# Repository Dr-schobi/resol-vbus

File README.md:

# resol-vbus

#### A JavaScript library for processing RESOL VBus data.

## Library is in maintenance mode!

> ...
>
> As a result of this shift of focus the resol-vbus library has entered maintenance mode. It will still receive security update when necessary over the course of the next months, but no additional improvements will be implemented here.
>
> ...

See [this issue](https://github.com/danielwippermann/resol-vbus/issues/110) for details.

## Features

* Connects to various RESOL VBus devices
* Processes live and recorded VBus data streams
* Discovers LAN-enabled RESOL devices on the local network
* Allows to send parameterization commands to a controller
* Synchronizes recorded VBus data from a RESOL datalogger to your local file system
* Converts recorded VBus data into human or machine readable formats, optionally allowing to filter the output

## Documentation

You can find the work-in-progress documentation for this project here:

[http://danielwippermann.github.io/resol-vbus/](http://danielwippermann.github.io/resol-vbus/)

The JSDoc-generated documentation is located here:

[http://danielwippermann.github.io/resol-vbus/#/jsdoc](http://danielwippermann.github.io/resol-vbus/#/jsdoc)

## Installation

If you want to use this module in your own application, you can just install it from the npm registry:

	⌘  npm install --save resol-vbus

If you want to contribute to it you might want to check out the latest version from GitHub:

	⌘  git clone https://github.com/danielwippermann/resol-vbus.git
	⌘  cd resol-vbus
	⌘  npm install

## Running the console examples

	⌘  node examples/<name>/index.js

## Running the tests

To start a single run of the test suite just enter the following command
into your shell:

	⌘  npm test

To run the tests after each change to the source just enter the
following command into your shell:

	⌘  npm test -- --watch

## Supported Devices & Services

* [All current RESOL controllers with VBus](http://www.resol.de/index/produkte/sprache/en)
* [RESOL DL2 Datalogger](http://www.resol.de/index/produktdetail/kategorie/2/sprache/en/id/12)
* [RESOL DL3 Datalogger](http://www.resol.de/index/produktdetail/kategorie/2/sprache/en/id/86)
* [RESOL KM2 Communication module](http://www.resol.de/index/produktdetail/kategorie/2/id/209/sprache/en)
* [RESOL VBus/LAN interface adapter](http://www.resol.de/index/produktdetail/kategorie/2/id/76/sprache/en)
* [RESOL VBus/USB interface adapter](http://www.resol.de/index/produktdetail/kategorie/2/id/13/sprache/en)
* [RESOL VBus.net](http://www.vbus.net/)

## Technical Information & Specifications

* [RESOL VBus Google Group](https://groups.google.com/forum/#!forum/resol-vbus)
* [RESOL VBus Protocol Specification](http://danielwippermann.github.io/resol-vbus/#/md/docs/vbus-specification)
* [RESOL VBus Packet List](http://danielwippermann.github.io/resol-vbus/#/vsf)
* [RESOL VBus Recording File Format](http://danielwippermann.github.io/resol-vbus/#/md/docs/vbus-recording-file-format)
* [RESOL VBus Specification File Format v1](http://danielwippermann.github.io/resol-vbus/#/md/docs/vbus-specification-file-format-v1)
* [RESOL VBus over TCP Specification](http://danielwippermann.github.io/resol-vbus/#/md/docs/vbus-over-tcp)
* [RESOL DL2 (v2) & DL3 Data Download API](http://danielwippermann.github.io/resol-vbus/#/md/docs/dlx-data-download-api)

## Known issues

- The `ConfigurationOptimizers` do not yet detect the firmware version running on the controller to be configured.
  That sometimes causes configuration loads and saves to fail because unknown values are read from or written to
  (e.g. using the "customizer" example on a DeltaSol MX with firmware version 1.11 or below).

## Projects using `resol-vbus`

- https://github.com/BenniG82/vbus-to-homie

## Changelog

## Version 0.29.0 (2024-01-22)

- [BREAKING CHANGE] Changed IPv6 device discovery support activation.
    Previously the `options` object passed into `TcpDataSourceProvider#discoverDevices`
    needed an `ipv6` boolean value set to `true`. That option was removed in favor of a
    `family` string value which defaults to `"IPv4"` but can be set to `"IPv6"` to
    perform a IPv6 device discovery. In that case the two other options `localAddress`
    and `broadcastInterface` are required as well. See the documentation for more details.
- Add verifiers for VBus-over-TCP commands to `TcpConnectionEndpoint`.
- Add `connectionAttemptFailed` event to `TcpConnectionEndpoint`.

## Version 0.28.0 (2024-01-06)

- Add `extendFieldData` option to `DLxJsonConverter`.
- Add `SpecificationFile#getPacketTemplate`.
- Add password and channel checks to TCP endpoint. (#93)
- Add `TcpConnection#disableReconnect`.
- Correctly propagate errors during `TcpConnection` reconnect.

## Version 0.27.0 (2022-03-09)

- Fix bugs in `SerialConnection` and `SerialDataSourceProvider`

## Version 0.26.0 (2022-12-18, never released publicly)

- [BREAKING CHANGE] Removed `Recorder`, `DLxRecorder` and `FileSystemRecorder`
    The `Recorder` style of interfaces was not well thought out and unreliable. This
    version removes it, with no replacement!
- [BREAKING CHANGE] Removed `lodash` dependency
    Although this removal was done with great caution and a lot of test coverage, there
    might be side effects we have not thought of.

## Version 0.25.0 (2022-04-12)

- Update several dependencies to fix security issues.
- Update VBus specification file to 20220206.
- Add support for CRC7 in protocols using minor version 1.
- Add `Datagram` and `Telegram` support to `VBusRecordingConverter`.

## Version 0.24.0 (2021-09-12)

- [BREAKING CHANGE] Replaced the deprecated "request" dependency with Fetch API impl
    Since the "request" dependency that was used in the `DLxRecorder` class has
    been deprecated, the code was refactored to use a Fetch API implementation instead.
    But since the method `DLxRecorder#downloadToStream` expected "request"-specific options,
    it had to be changed, too. This method was renamed to `DLxRecorder#_downloadToStream` to
    indicate that it is a class-private method and its signature was changed to accept
    Fetch API specific options.

## Version 0.23.0 (2021-05-14)

- [BREAKING CHANGE] Replacing custom inheritance code with `class` syntax
    Up to this version inheritance was established using a custom `extend` function.
    Since only modern ECMAscript runtimes are supported since the last release the code was
    refactored to use the ECMAscript `class` syntax instead. In that process the `extend`
    function was removed, both the standalone one and the static class function that was
    added to every "class".
- [BREAKING CHANGE] Returning a `Promise` from `channelListCallback` callback
    The `TcpConnection` accepts a `channelListCallback`. This callback gets called with the
    list of channels returned from the `CHANNELLIST` command and a `done` callback.

    Up to this version the return value of the `channelListCallback` was ignored. Starting
    with this version this behaviour is changed if the return value of the callback is
    a `Promise`:
    - if the `Promise` reject, the `done` callback is automatically called with `done(reason)`
    - if the `Promise` resolves, the `done` callback is automatically called with
      `done(null, result)`

    This allows the `channelListCallback` to be `async`.
- Errors thrown by `TcpConnection#connect` now have a `vbusPhase` member describing on which
  VBus-over-TCP command the error occurred

## Version 0.22.0 (2021-05-10)

- [BREAKING CHANGE] Dropping support for Node.js versions < 12

## Version 0.21.0 (2020-05-02)

- [BREAKING CHANGE] Returning a `Promise` from `filterPacket` or `filterDatagram` callbacks
    The `Connection#transceive` method and many of the helper methods that use it
    accept a `filterPacket` and/or `filterDatagram` callback. Those callbacks get called
    with the data to filter and a `done` callback.

    Up to this version the return value of the filter callbacks was ignored. Starting with
    this version this behaviour is changed if the return value of the filter callbacks is
    a `Promise`:
    - if the `Promise` rejects, the `done` callback is automatically called with `done(reason)`
    - if the `Promise` resolves with `null` or `undefined`, the `done` callback is not called
    - if the `Promise` resolves with any other result, the `done` callback is automatically
      called with `done(null, result)`

    This allows `async` filter callbacks!
- Add `SerialConnection#baudrate` option.
- Stop running Travis tests under Node 6.
    Some dependency of `jest` does not work under Node 6 making tests break
    for that target. The `resol-vbus` library itself might still work under
    Node 6, but there is no guarantee...

## Version 0.20.0 (2019-06-15)

- This version contains several breaking changes! You have been warned...
	- Refactor code to make use of ES2018 features (using Babel to back-support up to Node.js 6)
	- Remove custom `Promise` implementation in favor of built-in, native one.
	- `Promise` return values no longer provide the `finally` and `done` methods.
	- Remove `utils.promise`, `utils.Promise` and `utils.cancelablePromise`.
	- Add `reportProgress` and `checkCanceled` options to `ConnectionCustomizer#transceive{Configuration,Value}` as a replacement to the previously used `cancelablePromise` solution.
- Add RESOL DeltaSol C configuration optimizer.
- Add support for VBus-over-TCP wrapped in TLS.

## Version 0.17.0 (2018-02-10)

- Add `Buffer` support to `Connection#(get|set)ValueById` for values larger than 32-bit.
- Add `Connection#getCaps1`.
- Add bulk value transaction support to `Connection` class.
- Add support to generate and parse "type 9" comment records using `VBusRecordingConverter`.
- Make it easier to create a `Specification` from a `SpecificationFile`.
- Extend `vbustouch-proxy` example with text data logging feature.
- Update dependencies.
- Some minor bug fixes.

### Version 0.16.0 (2017-02-01)

- Use VSF binary file to load VBus specification data
- Add support to read and write raw data in VBus recordings
- Extend `VBusRecordingConverter` to support fast topology-only scan
- Code clean up
- Several minor bug fixes

### Version 0.15.0 (2016-03-30)

- Update VBus specification data
- Several minor bug fixes

### Version 0.14.0 (2015-10-29)

- Improve configuration optimizers and their discovery
- Update VBus specification data

### Version 0.13.0 (2015-05-14)

- Add configuration optimizers for RESOL DeltaSol SLT
- Add BlockType support

### Version 0.12.2 (2015-05-05)

- Update VBus specification data

### Version 0.12.1 (2015-04-27)

- Add configuration optimizers for RESOL DeltaSol MX and BS/4 v2
- Add a simple JSON live data server example
- Add some documentation
- Several bug fixes

### Version 0.12.0 (2015-02-28)

- Add `vbustouch-proxy` example
- Add support for rounding floating point numbers

### Version 0.11.1 (2014-11-04)

- Fix a floating point bug caused by `setRawValue`

### Version 0.11.0 (2014-10-29)

- Added support for setting packet field values
- Several bug fixes

### Version 0.10.0 (2014-04-26)

- Finalized support for customizing controller configuration.
- Several bug fixes.

### Version 0.9.0 (2014-03-16)

- Completed Recorder class by adding support for recording
- Added unit conversion to VBus specification
- Several bug fixes.

### Version 0.8.0 (2014-03-03)

- Extended Converter and VBusRecordingConverter to support object mode in stream (for performance reason)
- Fixed several bugs
- Increased test coverage and completed documentation.

### Version 0.7.0 (2014-02-17)

First release to the NPM registry.

## Contributors

* Thorsten Müller
* Paul Hanna
* Sabine Käß
* Andrew Thompson (@thompsa)
* @t9zx
* @SurfGargano
* @epenet

## Legal Notices

RESOL, VBus, VBus.net and others are trademarks or registered trademarks
of RESOL - Elektronische Regelungen GmbH.

All other trademarks are the property of their respective owners.

## License

The MIT License (MIT)

Copyright (c) 2013-present, Daniel Wippermann.

Permission is hereby granted, free of charge, to any person obtaining a copy
of this software and associated documentation files (the "Software"), to deal
in the Software without restriction, including without limitation the rights
to use, copy, modify, merge, publish, distribute, sublicense, and/or sell
copies of the Software, and to permit persons to whom the Software is
furnished to do so, subject to the following conditions:

The above copyright notice and this permission notice shall be included in
all copies or substantial portions of the Software.

THE SOFTWARE IS PROVIDED "AS IS", WITHOUT WARRANTY OF ANY KIND, EXPRESS OR
IMPLIED, INCLUDING BUT NOT LIMITED TO THE WARRANTIES OF MERCHANTABILITY,
FITNESS FOR A PARTICULAR PURPOSE AND NONINFRINGEMENT. IN NO EVENT SHALL THE
AUTHORS OR COPYRIGHT HOLDERS BE LIABLE FOR ANY CLAIM, DAMAGES OR OTHER
LIABILITY, WHETHER IN AN ACTION OF CONTRACT, TORT OR OTHERWISE, ARISING FROM,
OUT OF OR IN CONNECTION WITH THE SOFTWARE OR THE USE OR OTHER DEALINGS IN
THE SOFTWARE.

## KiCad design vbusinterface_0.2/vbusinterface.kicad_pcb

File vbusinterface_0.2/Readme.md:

## Version 0.2 (2023-08)

While cleaning up, I came across the box of materials for this project and decided to finish this project.
The wires of the flying installation verion 0.0 have broken off in the meantime and the system was not operational.

Changes:
- re-draw with a new Kicad version (I wouldn't say I have lost them, but I stopped searching for the old files)
- integrate connectors, use [Wago 2604-1102](https://www.wago.com/global/pcb-terminal-blocks-and-pluggable-connectors/pcb-terminal-block/p/2604-1102)
- try to have it mostly assembled from JLCPCB to avoid stocking 10s of some exotic SMD components
- use an off-the shelf PoE splitter for providing the 5V without extra power supplies, option of barrel jack or micro-USB power connector
- integrate a mounting system, I decided to use the Phoenix Contact UMK system to have a DIN rail mount for everything. This requires [UMK-BE22.5](https://www.phoenixcontact.com/en-pc/products/base-element-umk-be-225-2970028), [UMK-SE11,25-3](https://www.phoenixcontact.com/en-pc/products/side-element-umk-se-1125-3-5030266), [UMK-11,25-1](https://www.phoenixcontact.com/en-pc/products/side-element-umk-se-1125-1-2970442) and [UMK-FE](https://www.phoenixcontact.com/en-pc/products/foot-element-umk-fe-2970031). This is a really cool configurable system which results in a really neat and sturdy mounting. (RANT:) However, the Phoenix Contact Website is completely useless for selecting which components one might want to use. There is no "compatible with" indication, no online configurator, not even a small quantity ordering process. I'm sure when I call them in a commercial setting from my day-job, a representative will show up immediately and explain the system to me. But as a hobbyist, this is unreachable. Individual parts online are more expensive than the assembled PCB. Sorry Phoenix Contact, but you've scared me away for any future use, even in my day-job.

really nice partially assembled PCBs as they arrived from JLCPCB

not so nice any more - with the needed fixes integrated

This is how the final system should look like. With options for USB-C and barrel-Jack power:

Conclusion:
- much nicer, but I introduced some errors
- when changing a few parts, even more can likely be assembled from "basic parts" directly, sparing me a load of new bags with individual SMD components

Errata:
- when designing a new component with Kicad, the default hole diameter is too small to fit a standard pin header. I had to use individual pieces of 0.4mm wire to mount my components U4 and U5
- the output to the TCP232 should be 3.3V only, but I was powering the 4093 stage with 5V. R3 needs to match. 
- for C1, I picked the wrong part from JLCPCB, should be 1nF instead of 1uF

(RANT on JLCPCB:) the JLCPCB parts selection is broken for me. For example, when searching for a "0805" resistor with a specific value, the parametric search does not gives too many results. When limiting to "basic parts" only, tjhe list is empty. Listing all "basic parts" "0805" resistors is possible, but they can't be sorted, the actual values in the list are cut off (I need to click though every part?). The Kicad Export with the Fabrication Toolkit is a really nice new way for single click export. But somehow the ICs are rotated the wrong way and the board dimensions for backside assembly are mixed up... In the end, this is still the best manufacturer for me, but I hesitate to pay more for shipping than for the product.

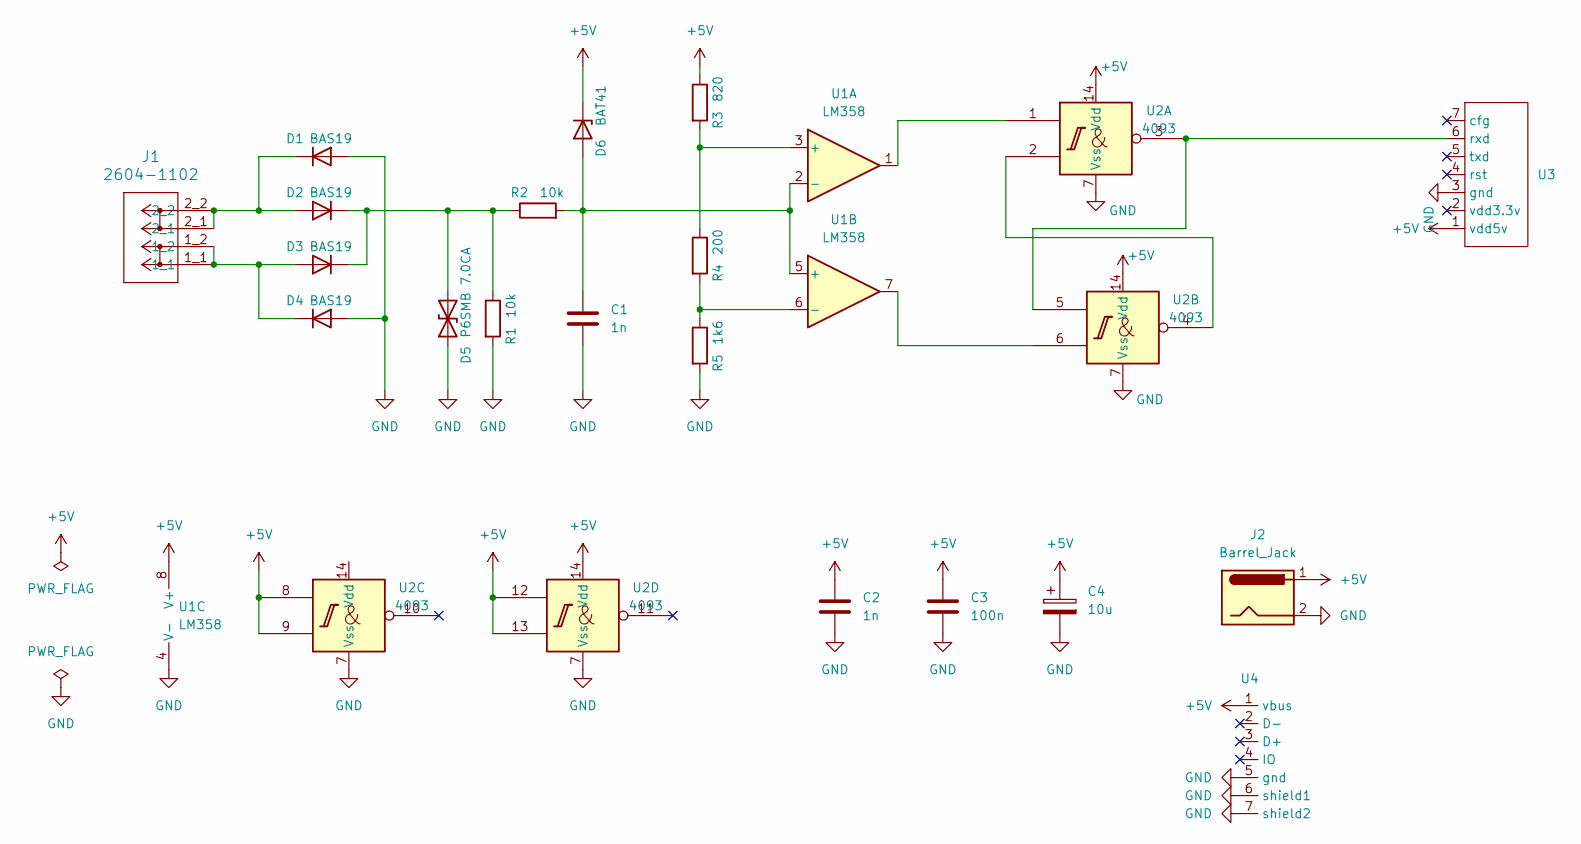
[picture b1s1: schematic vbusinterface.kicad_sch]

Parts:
C1, C2: 1n; C_0805_2012Metric; LCSC Part # C28323
C3: 100n; C_0805_2012Metric; LCSC Part # C49678
C4: 10u; C_0805_2012Metric; LCSC Part # C15850
D1, D2, D3, D4: BAS19; SOT-23; LCSC Part # C68960
D5: P6SMB 7.0CA; D_SMB; LCSC Part # C78395
D6: BAT41; D_SOD-123; LCSC Part # C222251
J1: 2604-1102; CONN_2604-1102_WAG
J2: Barrel_Jack; BarrelJack_Kycon_KLDX-0202-xC_Horizontal
R1, R2: 10k; R_0805_2012Metric; LCSC Part # C17414
R3: 820; R_0805_2012Metric; LCSC Part # C17837
R4: 200; R_0805_2012Metric; LCSC Part # C17540
R5: 1k6; R_0805_2012Metric; LCSC Part # C352253
U1: LM358; SOIC-8_3.9x4.9mm_P1.27mm; LCSC Part # C7950
U2: 4093; SOIC-14_3.9x8.7mm_P1.27mm; LCSC Part # C7867
U3: usrtcp232-t2
U4: usbpwr

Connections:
+5V: C2.1, C3.1, C4.1, D6.1 (K), J2.1, R3.1, U1.8 (V+), U2.8, U2.9, U2.12, U2.13, U2.14 (Vdd), U3.1 (vdd5v), U4.1 (vbus)
GND: C1.2, C2.2, C3.2, C4.2, D1.1 (A), D4.1 (A), D5.1 (A1), J2.2, R1.2, R5.2, U1.4 (V-), U2.7 (Vss), U3.3 (gnd), U4.5 (gnd), U4.6 (shield1), U4.7 (shield2)
unnamed: D1.3 (K), D2.1 (A), J1.2_1, J1.2_2
unnamed: D2.3 (K), D3.3 (K), D5.2 (A2), R1.1, R2.1
unnamed: D3.1 (A), D4.3 (K), J1.1_1, J1.1_2
unnamed: C1.1, D6.2 (A), R2.2, U1.2 (-), U1.5 (+)
unnamed: U1.1, U2.1
unnamed: U1.7, U2.6
unnamed: R3.2, R4.1, U1.3 (+)
unnamed: R4.2, R5.1, U1.6 (-)
unnamed: U2.2, U2.4
unnamed: U2.3, U2.5, U3.6 (rxd)

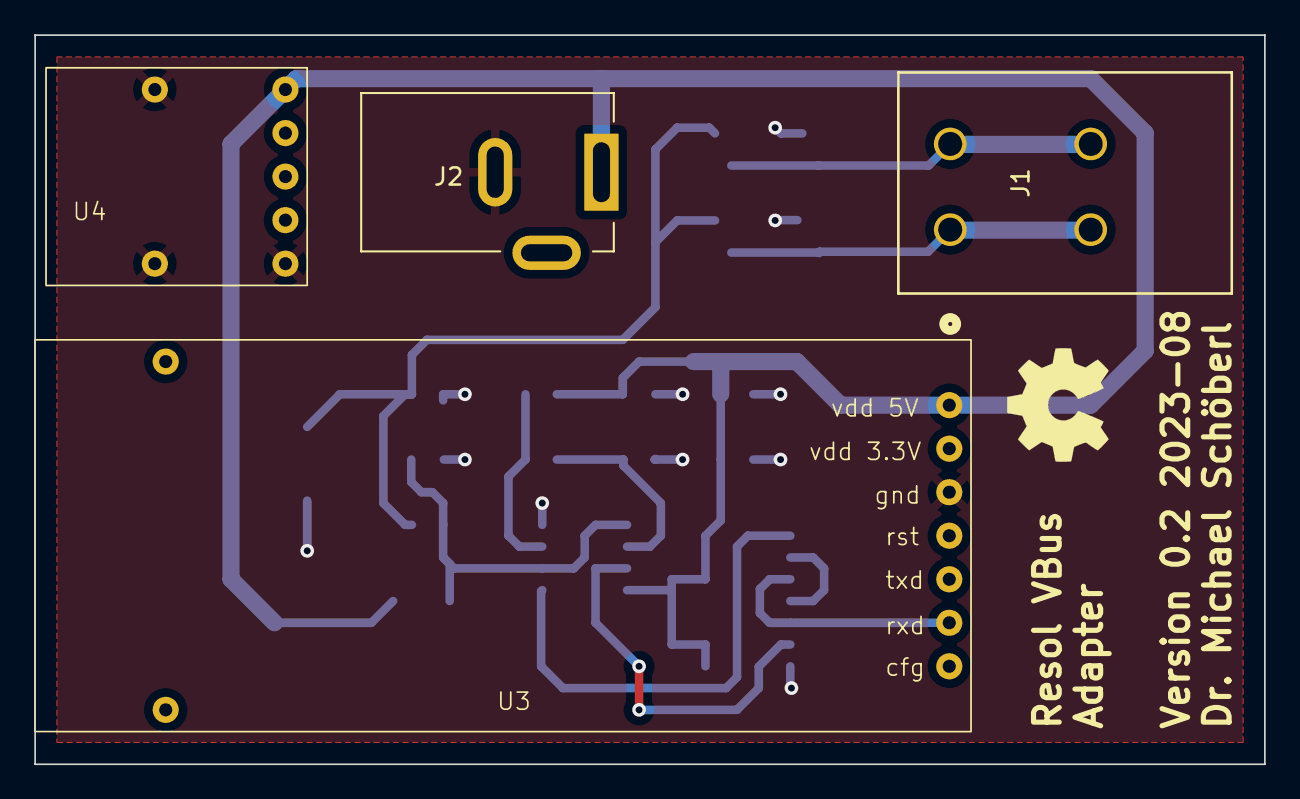
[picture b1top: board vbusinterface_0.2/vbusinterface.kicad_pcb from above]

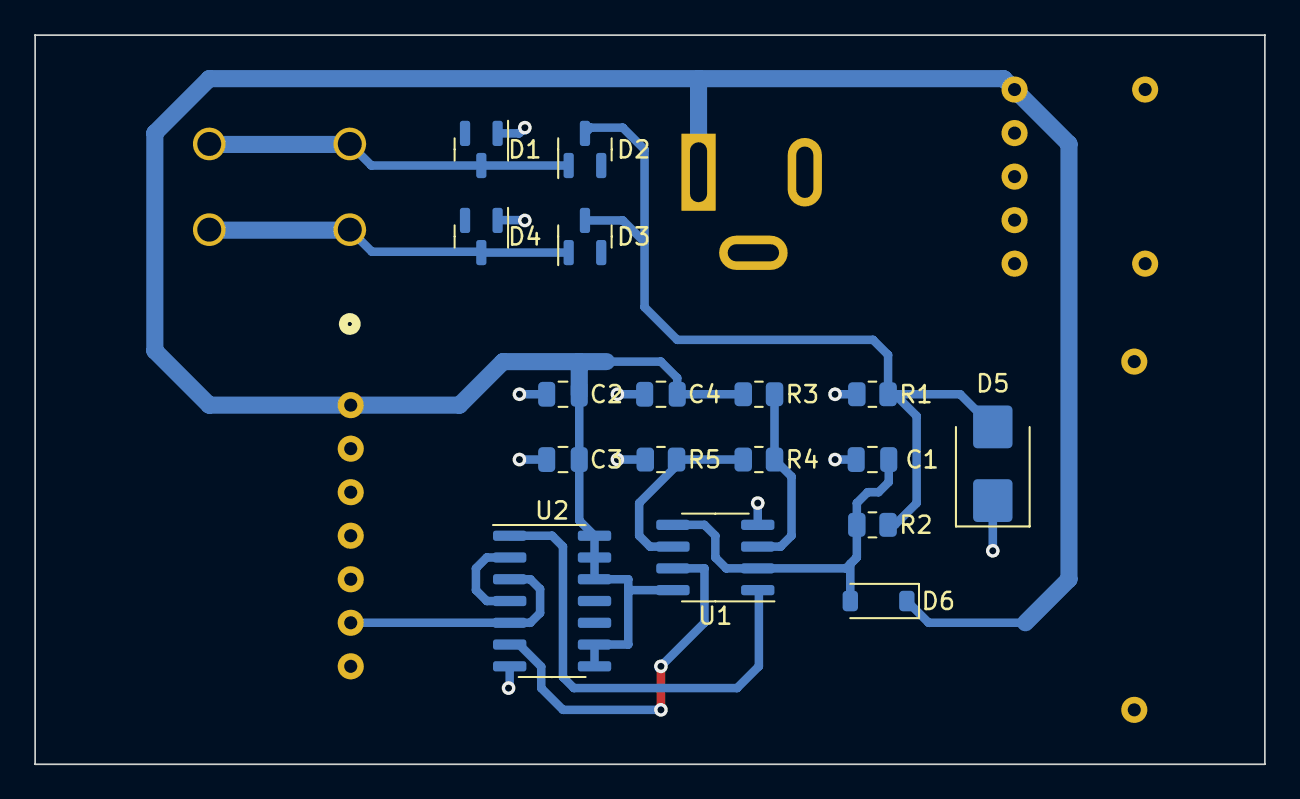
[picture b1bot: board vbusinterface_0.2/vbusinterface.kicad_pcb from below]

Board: 2 copper layers, 71.8 x 42.5 mm, 21 parts (17 on the bottom side), 12 nets.

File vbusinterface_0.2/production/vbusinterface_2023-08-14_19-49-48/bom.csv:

Designator,Footprint,Quantity,Value,LCSC Part #
"C1, C2",0805,2,1n,C28323
C3,0805,1,100n,C49678
C4,0805,1,10u,C15850
"D1, D2, D3, D4",SOT-23,4,BAS19,C68960
D5,D_SMB,1,P6SMB 7.0CA,C78395
D6,D_SOD-123,1,BAT41,C222251
J1,CONN_2604-1102_WAG,1,2604-1102,
J2,BarrelJack_Kycon_KLDX-0202-xC_Horizontal,1,Barrel_Jack,
"R1, R2",0805,2,10k,C17414
R3,0805,1,820,C17837
R4,0805,1,200,C17540
R5,0805,1,1k6,C352253
U1,SOIC-8_3.9x4.9mm_P1.27mm,1,LM358,C7950
U2,SOIC-14_3.9x8.7mm_P1.27mm,1,4093,C7867
U3,usrtcp232-t2,1,~,
U4,usbpwr,1,~,

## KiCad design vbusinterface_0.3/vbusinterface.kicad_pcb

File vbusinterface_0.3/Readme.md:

# Version 0.3 (2023-08)

Changes:
- small redesign based on errata from v0.2,
- more basic parts assembled from JLCPCB directly

Status: pcb has arrived and is finally assembled and ready for use!

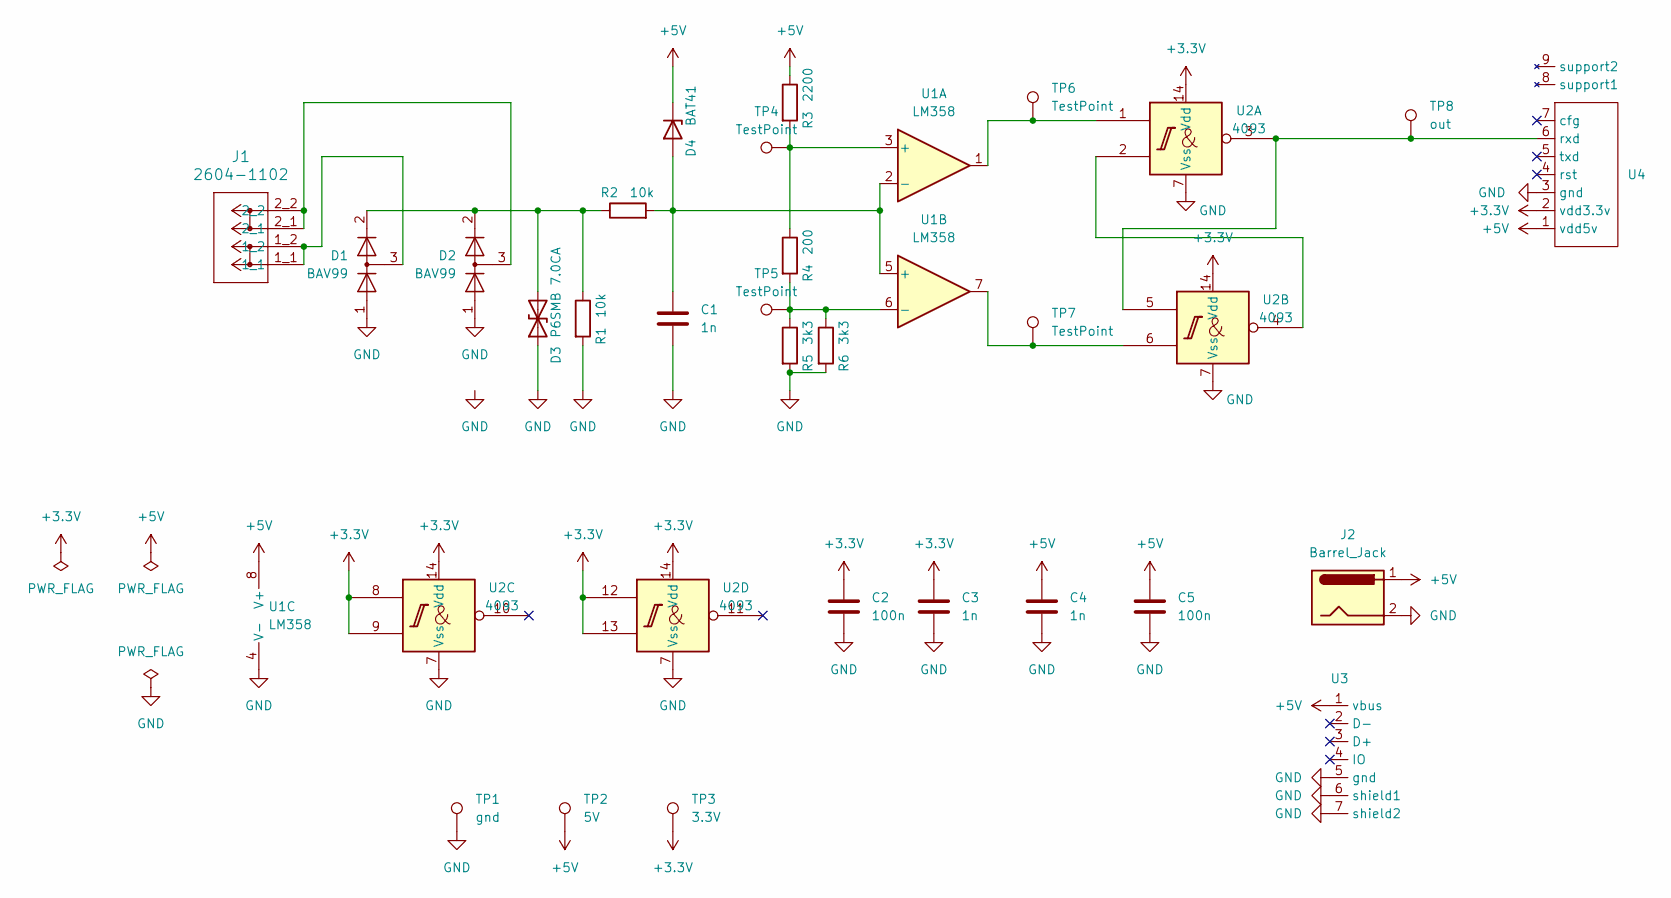
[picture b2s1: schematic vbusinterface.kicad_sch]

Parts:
C1, C3, C4: 1n; C_0805_2012Metric; LCSC C46653
C2, C5: 100n; C_0805_2012Metric; LCSC C49678
D1, D2: BAV99; SOT-23; LCSC C2500
D3: P6SMB 7.0CA; D_SMB; LCSC C78395
D4: BAT41; D_SOD-123; LCSC C222251
J1: 2604-1102; CONN_2604-1102_WAG
J2: Barrel_Jack; BarrelJack_Kycon_KLDX-0202-xC_Horizontal
R1, R2: 10k; R_0805_2012Metric; LCSC C17414
R3: 2200; R_0805_2012Metric; LCSC C17520
R4: 200; R_0805_2012Metric; LCSC C17540
R5, R6: 3k3; R_0805_2012Metric; LCSC C26010
TP1: gnd; TestPoint_Pad_2.0x2.0mm
TP2: 5V; TestPoint_Pad_2.0x2.0mm
TP3: 3.3V; TestPoint_Pad_2.0x2.0mm
TP4, TP5, TP6, TP7: TestPoint; TestPoint_Pad_2.0x2.0mm
TP8: out; TestPoint_Pad_2.0x2.0mm
U1: LM358; SOIC-8_3.9x4.9mm_P1.27mm; LCSC C7950
U2: 4093; SOIC-14_3.9x8.7mm_P1.27mm; LCSC C7867
U3: usbpwr
U4: usrtcp232-t2

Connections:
+3.3V: C2.1, C3.1, TP3.1, U2.8, U2.9, U2.12, U2.13, U2.14 (Vdd), U4.2 (vdd3.3v)
+5V: C4.1, C5.1, D4.1 (K), J2.1, R3.1, TP2.1, U1.8 (V+), U3.1 (vbus), U4.1 (vdd5v)
GND: C1.2, C2.2, C3.2, C4.2, C5.2, D1.1 (K), D2.1 (K), D3.1 (A1), J2.2, R1.2, R5.2, R6.2, TP1.1, U1.4 (V-), U2.7 (Vss), U3.5 (gnd), U3.6 (shield1), U3.7 (shield2), U4.3 (gnd)
unnamed: D1.2 (A), D2.2 (A), D3.2 (A2), R1.1, R2.1
unnamed: D1.3 (K), J1.1_1, J1.1_2
unnamed: D2.3 (K), J1.2_1, J1.2_2
unnamed: C1.1, D4.2 (A), R2.2, U1.2 (-), U1.5 (+)
unnamed: TP6.1, U1.1, U2.1
unnamed: TP7.1, U1.7, U2.6
unnamed: R3.2, R4.1, TP4.1, U1.3 (+)
unnamed: R4.2, R5.1, R6.1, TP5.1, U1.6 (-)
unnamed: U2.2, U2.4
unnamed: TP8.1, U2.3, U2.5, U4.6 (rxd)

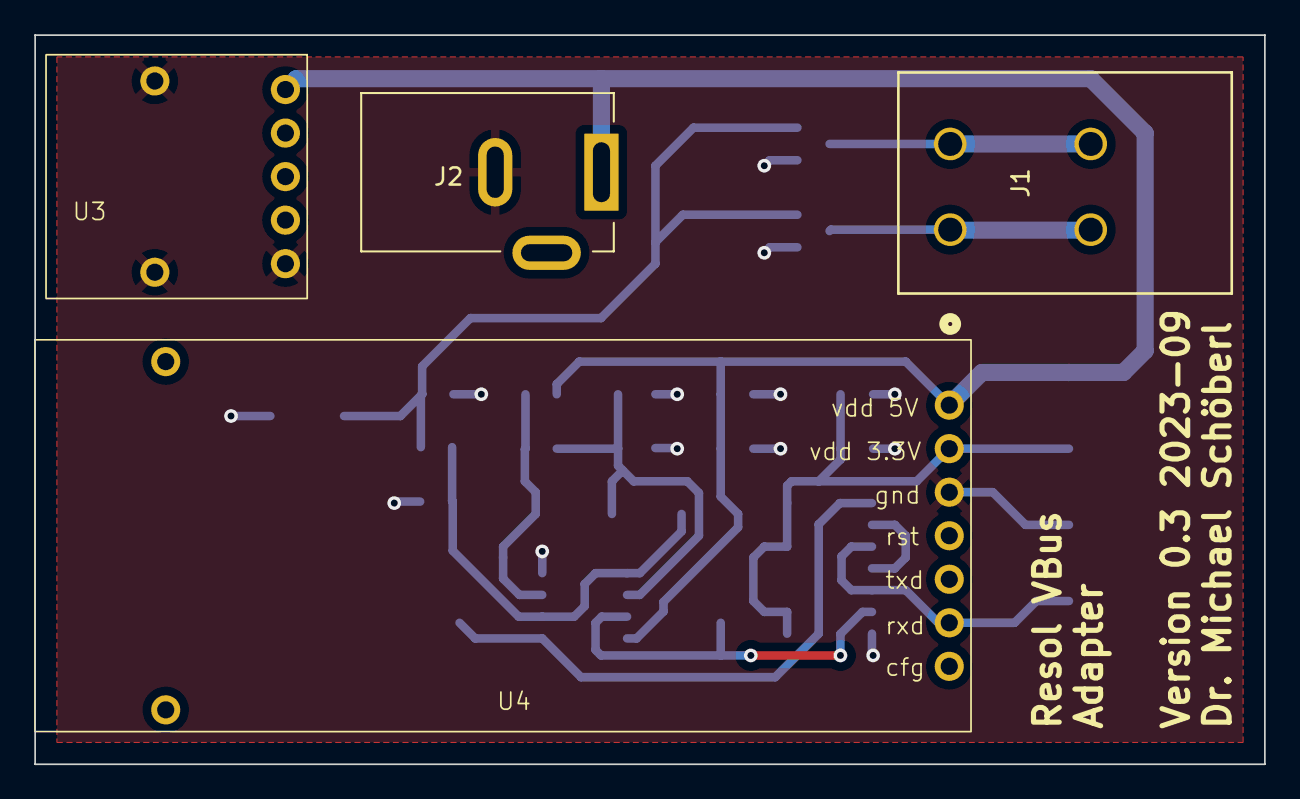
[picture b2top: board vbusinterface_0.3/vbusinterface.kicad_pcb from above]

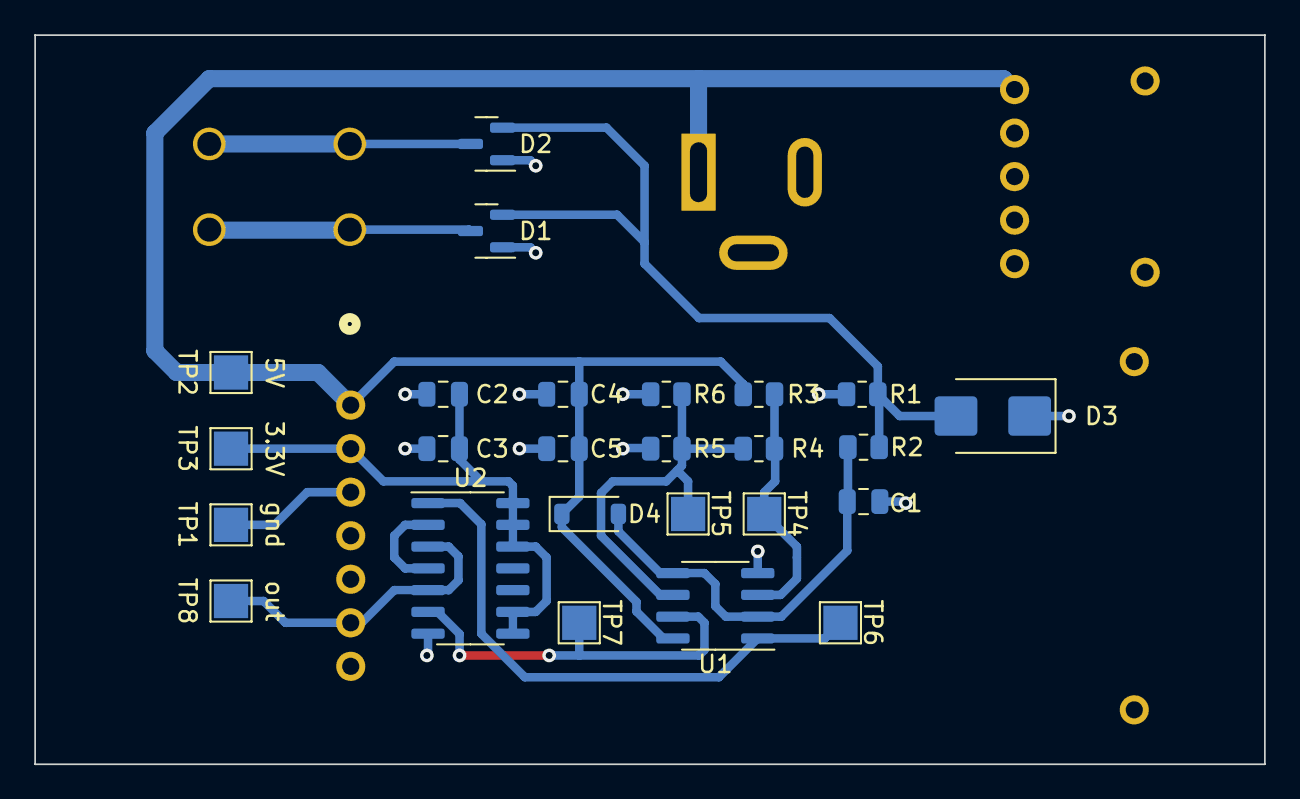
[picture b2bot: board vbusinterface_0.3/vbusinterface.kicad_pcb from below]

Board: 2 copper layers, 71.8 x 42.5 mm, 29 parts (25 on the bottom side), 13 nets.

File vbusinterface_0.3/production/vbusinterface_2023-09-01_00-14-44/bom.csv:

Designator,Footprint,Quantity,Value,LCSC Part #
"C1, C3, C4",0805,3,1n,C46653
"C2, C5",0805,2,100n,C49678
"D1, D2",SOT-23,2,BAV99,C2500
D3,D_SMB,1,P6SMB 7.0CA,C78395
D4,D_SOD-123,1,BAT41,C222251
J1,CONN_2604-1102_WAG,1,2604-1102,
J2,BarrelJack_Kycon_KLDX-0202-xC_Horizontal,1,Barrel_Jack,
"R1, R2",0805,2,10k,C17414
R3,0805,1,2200,C17520
R4,0805,1,200,C17540
"R5, R6",0805,2,3k3,C26010
TP1,TestPoint_Pad_2.0x2.0mm,1,gnd,
TP2,TestPoint_Pad_2.0x2.0mm,1,5V,
TP3,TestPoint_Pad_2.0x2.0mm,1,3.3V,
"TP4, TP5, TP6, TP7",TestPoint_Pad_2.0x2.0mm,4,TestPoint,
TP8,TestPoint_Pad_2.0x2.0mm,1,out,
U1,SOIC-8_3.9x4.9mm_P1.27mm,1,LM358,C7950
U2,SOIC-14_3.9x8.7mm_P1.27mm,1,4093,C7867
U3,usbpwr,1,~,
U4,usrtcp232-t2,1,~,

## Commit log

2023-09-01 initial files
2023-09-01 images for V0.0
2023-09-01 Update Readme.md
    update doc
2023-09-01 more images
2023-09-01 Update Readme.md
    more description
2023-09-01 Update Readme.md
    more descr
2023-09-01 Update Readme.md
    more docs
2023-09-01 more files/images
2023-09-01 ignore some
2023-09-01 ignore some more
2023-09-01 Create Readme.md
    split docs
2023-10-30 added new image
2025-03-08 Update README with maintenance mode notice.
2025-03-10 test
2025-03-10 add possible second connection
2025-03-10 added disconnect
2025-03-10 fix variable scope
2025-03-10 fix disconnect typo
2025-03-12 Added the option for a second connection (#112)
2025-03-12 Add support to set different channel for second connection.
2025-03-23 Update config.js.example
    extend example to explain second connection
